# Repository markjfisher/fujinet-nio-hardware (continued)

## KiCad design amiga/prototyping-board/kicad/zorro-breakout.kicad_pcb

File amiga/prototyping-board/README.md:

# Passive Amiga Zorro-II breakout — revision A

Open [kicad/zorro-breakout.kicad_pro](kicad/zorro-breakout.kicad_pro) in KiCad 10.
The schematic and PCB use project-local symbol and footprint libraries; no
downloaded library is required. All 100 physical edge contacts are exposed.
There are **no active components, buffers, level shifters, termination,
regulators, memory or AutoConfig logic**, and no development-module footprint.

**FABRICATION-READY for a prototype spin, not hardware-tested or production-qualified.**
Read [reference-review.md](docs/reference-review.md) for the pin-map corrections
and mechanical findings, and [fabrication notes](fabrication/README.md) before
using the fabrication outputs. Nothing has been ordered or manufactured.

The [two-layer conversion review](docs/two-layer-review.md) records the
before/after measurements, return-path trade-offs and cost limitations.

The follow-up [mechanical cross-check](docs/mechanical-cross-check.md) measures
VA2000, RIPPLE-IDE, AmigaSID and the EATX socket against this board and
Commodore drawings. A-5 controls the released geometry; PCBWay is the target
fabricator and WingTAT ED100BGFBK the mating socket. Actual seating/wipe and
host operation remain prototype validation items.

## Files

* `kicad/`: editable schematic, two-layer PCB, project and local libraries.
* `data/pin-map.csv`: independently transcribed/reviewed Appendix K pin map.
* `data/verification.csv`: each physical contact → net → footprint pad →
  every matching header/test-point pad, including shared grounds and +5V.
* `data/bom.csv`: passive assembly parts. Headers may be omitted for direct
  probe access or replaced with compatible 2.54 mm sockets.
* `review/`: schematic PDF, PCB views, ERC/DRC reports and consistency result.
* `fabrication/`: copper, mask, silk and outline Gerbers; Excellon drill file,
  drill map and fabrication instructions.
* `scripts/`: reproducible generation, routing import, verification and export.
* `routing/`: Specctra input/session retained to reproduce routed copper.

## Finding signals

View the **component side**, insertion edge down: pin 100 is at the left end,
pin 2 at the right. **Pin 1 is on the reverse, directly opposite pin 2.**
The board does not have a key that prevents reversed insertion. Verify your
A500-to-Zorro-II adapter's orientation before insertion. An A500's native
86-pin expansion connector is not this 100-pin connector.

| Header | Group | Rows, top to bottom |
|---|---|---|
| J2 | ADDRESS | A1–A23, GND |
| J3 | DATA | D0–D15, GND |
| J4 | BUS CONTROL | /AS, /UDS, /LDS, READ, /DTACK, /OVR, XRDY, /RESET, /HLT, /BERR, FC0, FC1, FC2, DOE, /BUSRST, GND |
| J5 | AUTOCONFIG / SLOT CONTROL | /SLAVE, /CFGIN, /CFGOUT, GND |
| J6 | INTERRUPTS | /INT2, /INT6, GND |
| J7 | DMA / ARBITRATION | /OWN, /BR, /BGACK, /BG, /GBG, GND |
| J8 | CLOCKS | /C3, CDAC, /C1, E, 7M, GND |
| J9 | POWER | +5V, +5V, GND, GND, GND, GND |
| J10 | RESERVED / LEGACY | Reserved 40, 42, 44, 96; legacy /VPA 48, /VMA 51; NC 97, 98; SenseZ3 91; GND |
| TP1 / TP2 / TP3 | Auxiliary POWER | -5V / +12V / -12V, respectively |

**On two-column headers, both pins in each horizontal pair carry the SAME
signal. They are not signal-and-ground pairs.** J4/J5/J6/J8 provide duplicate
access for a development connection and a logic analyser. The rectangular
pad is header pin 1; pairs are numbered 1/2, 3/4, etc. The numbers next to
signal names on the board are **Zorro contact numbers**, not header indices.
J9 similarly provides four +5V pins and eight ground pins.

Important corrections to the starting map: **28=A7, 29=A1**; 96 is Reserved
with a legacy /EINT1 alias. Pin 91 is **not** connected to the PCB ground
plane: only a Zorro-II backplane grounds it. See the reference review for all
aliases and the reason to distinguish physical names from Zorro-II names.

## Connecting and probing

**DO NOT CONNECT DIRECTLY TO 3.3V LOGIC WITHOUT CHECKING ELECTRICAL
COMPATIBILITY.** This applies to the Core2350B/RP2350B board, an ESP32-S3 and
the logic analyser itself. This breakout makes no electrical conversion or
protection. Provide the required external interface before attaching logic.

Power the Amiga off before inserting/removing the card or moving jumpers.
Check board orientation, shorts between supply rails and ground, and
continuity through the adapter before powering up. Do not feed a USB module's
5V supply back into the Amiga's +5V rail. The auxiliary rails are test-only;
their presence and current budget depend on the host/adapter.

Keep probe and jumper leads short and use a nearby labelled GND. Prefer
high-impedance, low-capacitance inputs; each attached probe/board adds bus
loading. Top/bottom GND pours help return paths but are interrupted by signal routing.
They do not provide the old uninterrupted inner plane or certify bus
timing or signal integrity. The routed stubs and external wiring must be
evaluated on the intended machine. This is not a ribbon-cable extension bus.
No rail output current rating has been established by a thermal test.

The card does not respond to AutoConfig, drive /SLAVE, request DMA, assert
an interrupt, or drive any clock/control signal by itself. **/CFGIN and
/CFGOUT are separate nets.** Inserting this passive board can interrupt
configuration of cards farther down the chain. For passive-only use with
downstream cards, an external jumper from J5.3 (/CFGIN) to J5.5 (/CFGOUT)
passes the chain through. Fit it only with power off and no external circuit
driving either line; remove it before testing external AutoConfig logic.
No jumper is fitted or implied by the design.

Reserved and NC contacts are brought out for completeness, not permission to
drive them. NC 97/98 can carry signals in Zorro-III operation. /VPA and /VMA
are legacy functions unavailable in A3000 Zorro-II cycles. SenseZ3 may float
on a Zorro-III backplane; this board deliberately adds no pull-up.

The board is 180 mm wide, 100 mm above the connector shoulder, with a
129.26 ±0.1 mm tongue projecting 7.62 mm, R1.5 roots and 1.5 ×45° planar
corner chamfers. Fingers are 1.6 ×5 mm with a 1 mm tip setback. Machine
0.5 ×45° per face; 0.6 mm centre land is a derived nominal reference only.
Continuous mask windows and selective hard gold are specified in the fabrication notes.
It omits an enclosure bracket and
full-length card guide tabs; support the board and attached leads during
bench use. Case/adapter fit and physical insertion have not been tested.

## Reproducing checks

From this directory in the workspace:

```sh
source ../../../../scripts/env.sh   # finds the workspace from its own location
python scripts/check.py
```

The check exports fresh schematic connectivity, runs the independent mapping
and geometry assertions (including five negative cases), then KiCad ERC and
DRC with schematic parity. It does not regenerate or reroute the board.
Reports include warnings and fail on any unresolved violation; no DRC/ERC
exclusions are added by this project. J1 alone allows intentional mask
bridges for the continuous gold-finger window.

To reproduce the CAD **overwriting generated design files**, run
`python scripts/generate.py`, followed by `python scripts/import-routing.py`
and the check above. Reuse the stored routing session only while connector
placement, nets and mechanics are unchanged. `generate.py` explicitly resets
the PCB to its placement/fan-out state; it must not be used to update text on
a manually edited board without preserving those edits first.

For a mechanical-only reapplication, `python scripts/mechanics.py` preserves
pad positions, nets and tracks/vias; it updates the outline, finger widths,
mask openings and local connector library without regenerating the schematic.
The generator also uses this mechanical definition. The stored routing session and hash-bound completion paths reproduce the
current two-layer board; see `routing/README.md`.

Routing uses local Freerouting 2.4.1 via DSN/SES. It is not needed for opening,
checking or exporting the finished project. See `routing/README.md` for the
exact command. `python scripts/export.py` rebuilds review/fabrication outputs
after the checks pass. No export script contacts a board manufacturer.

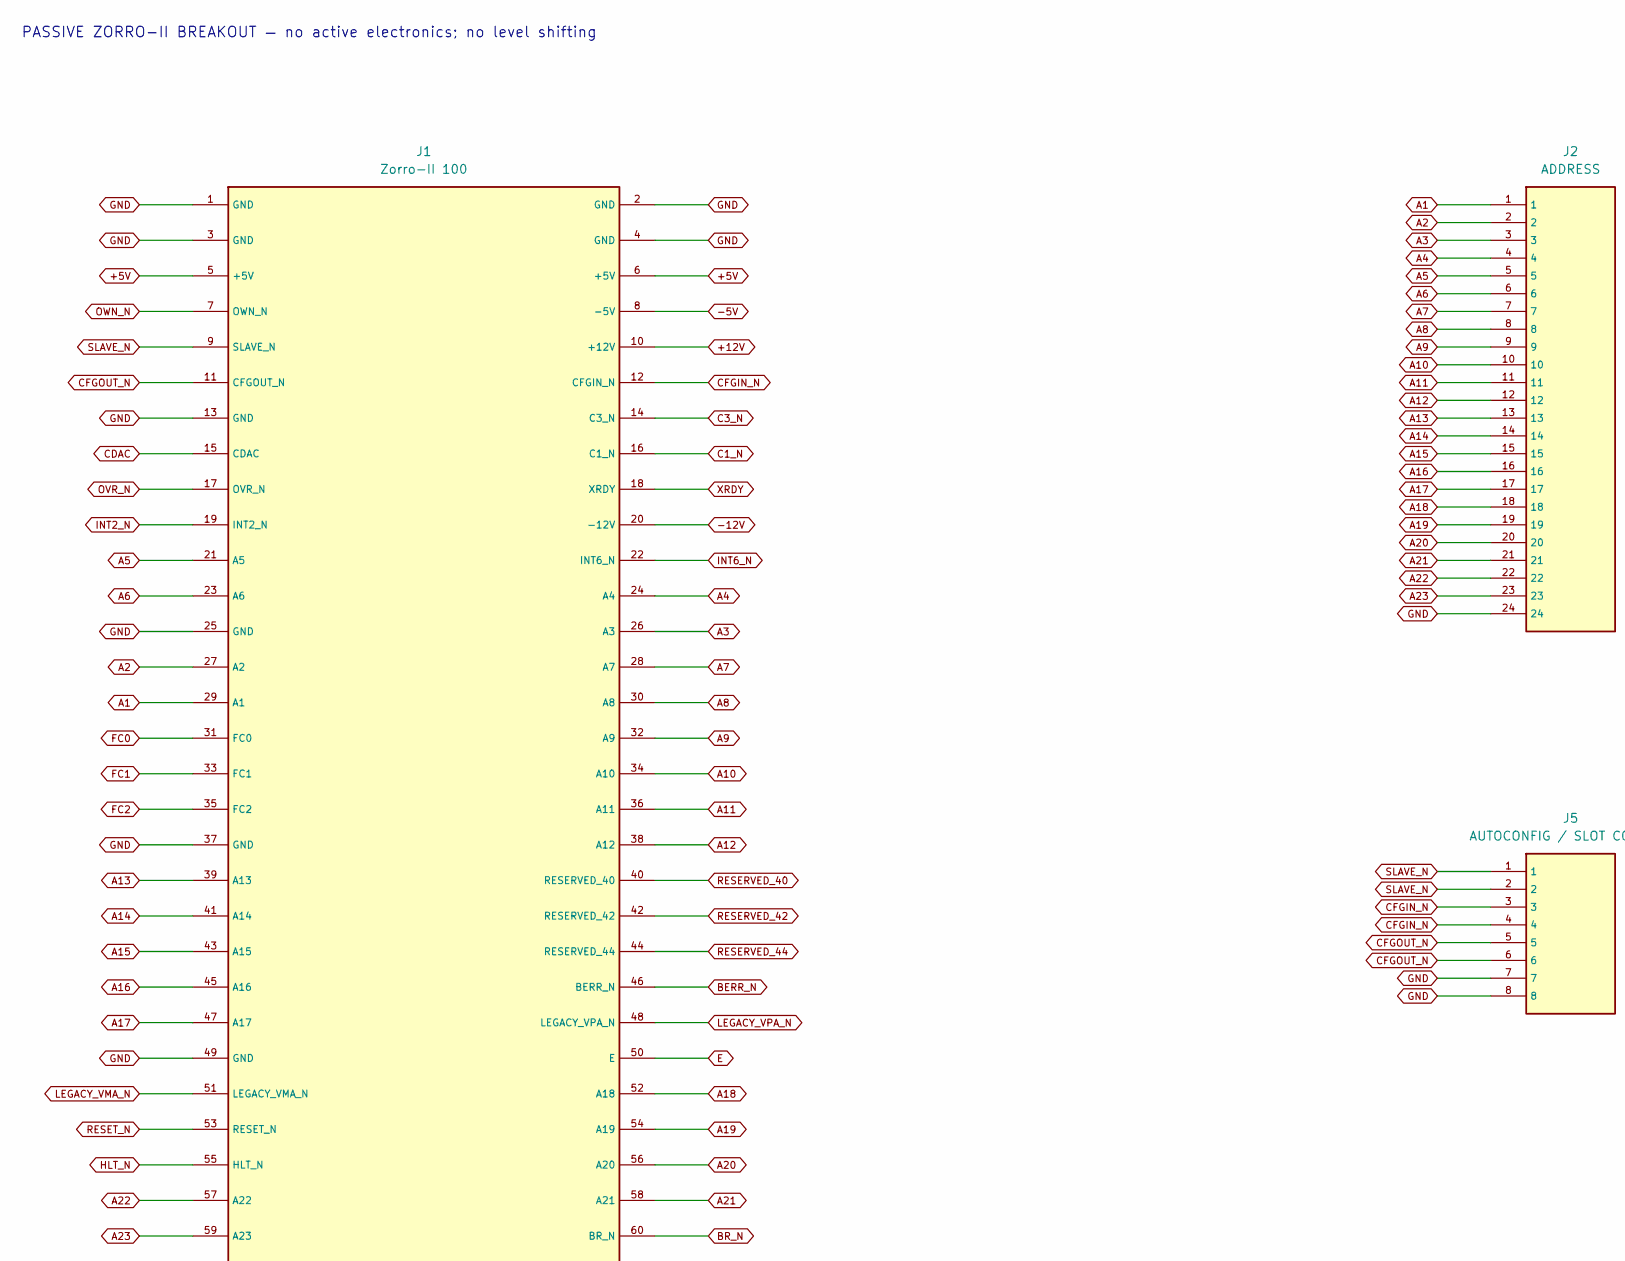
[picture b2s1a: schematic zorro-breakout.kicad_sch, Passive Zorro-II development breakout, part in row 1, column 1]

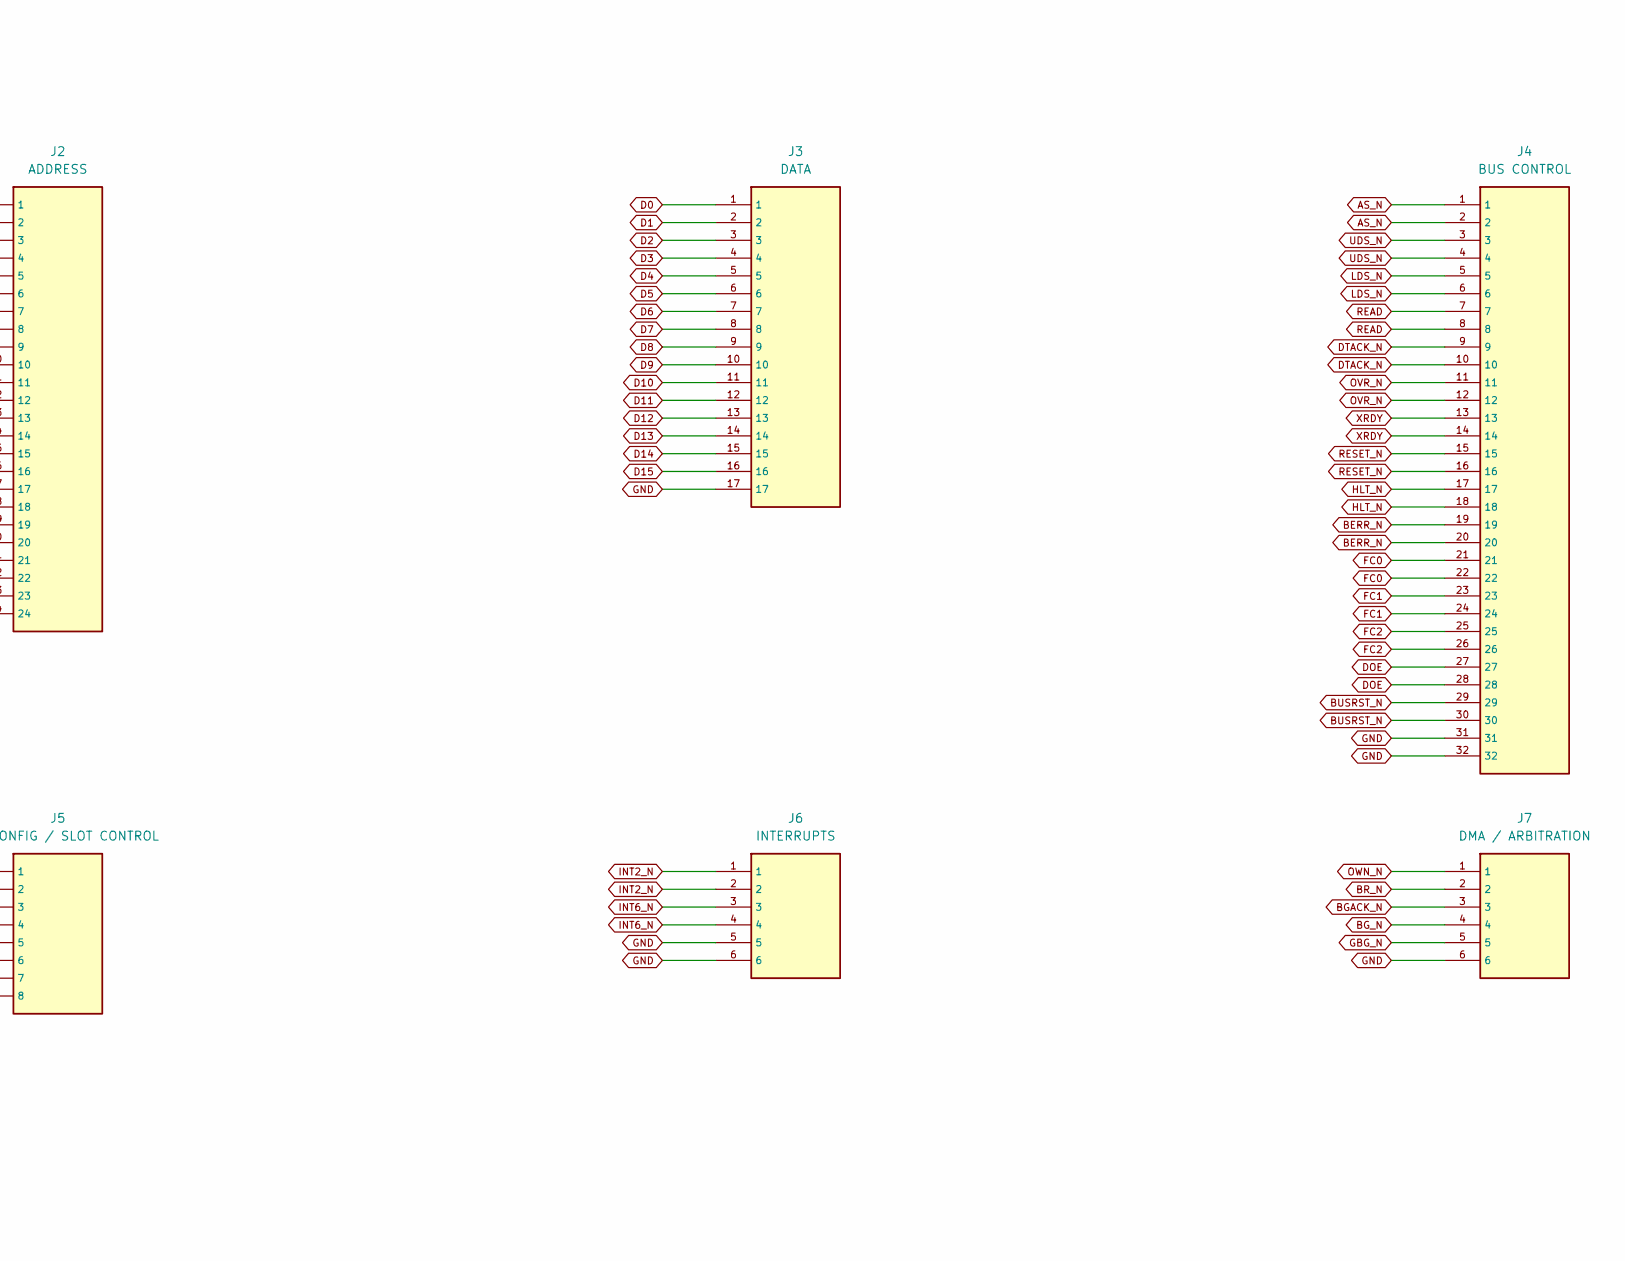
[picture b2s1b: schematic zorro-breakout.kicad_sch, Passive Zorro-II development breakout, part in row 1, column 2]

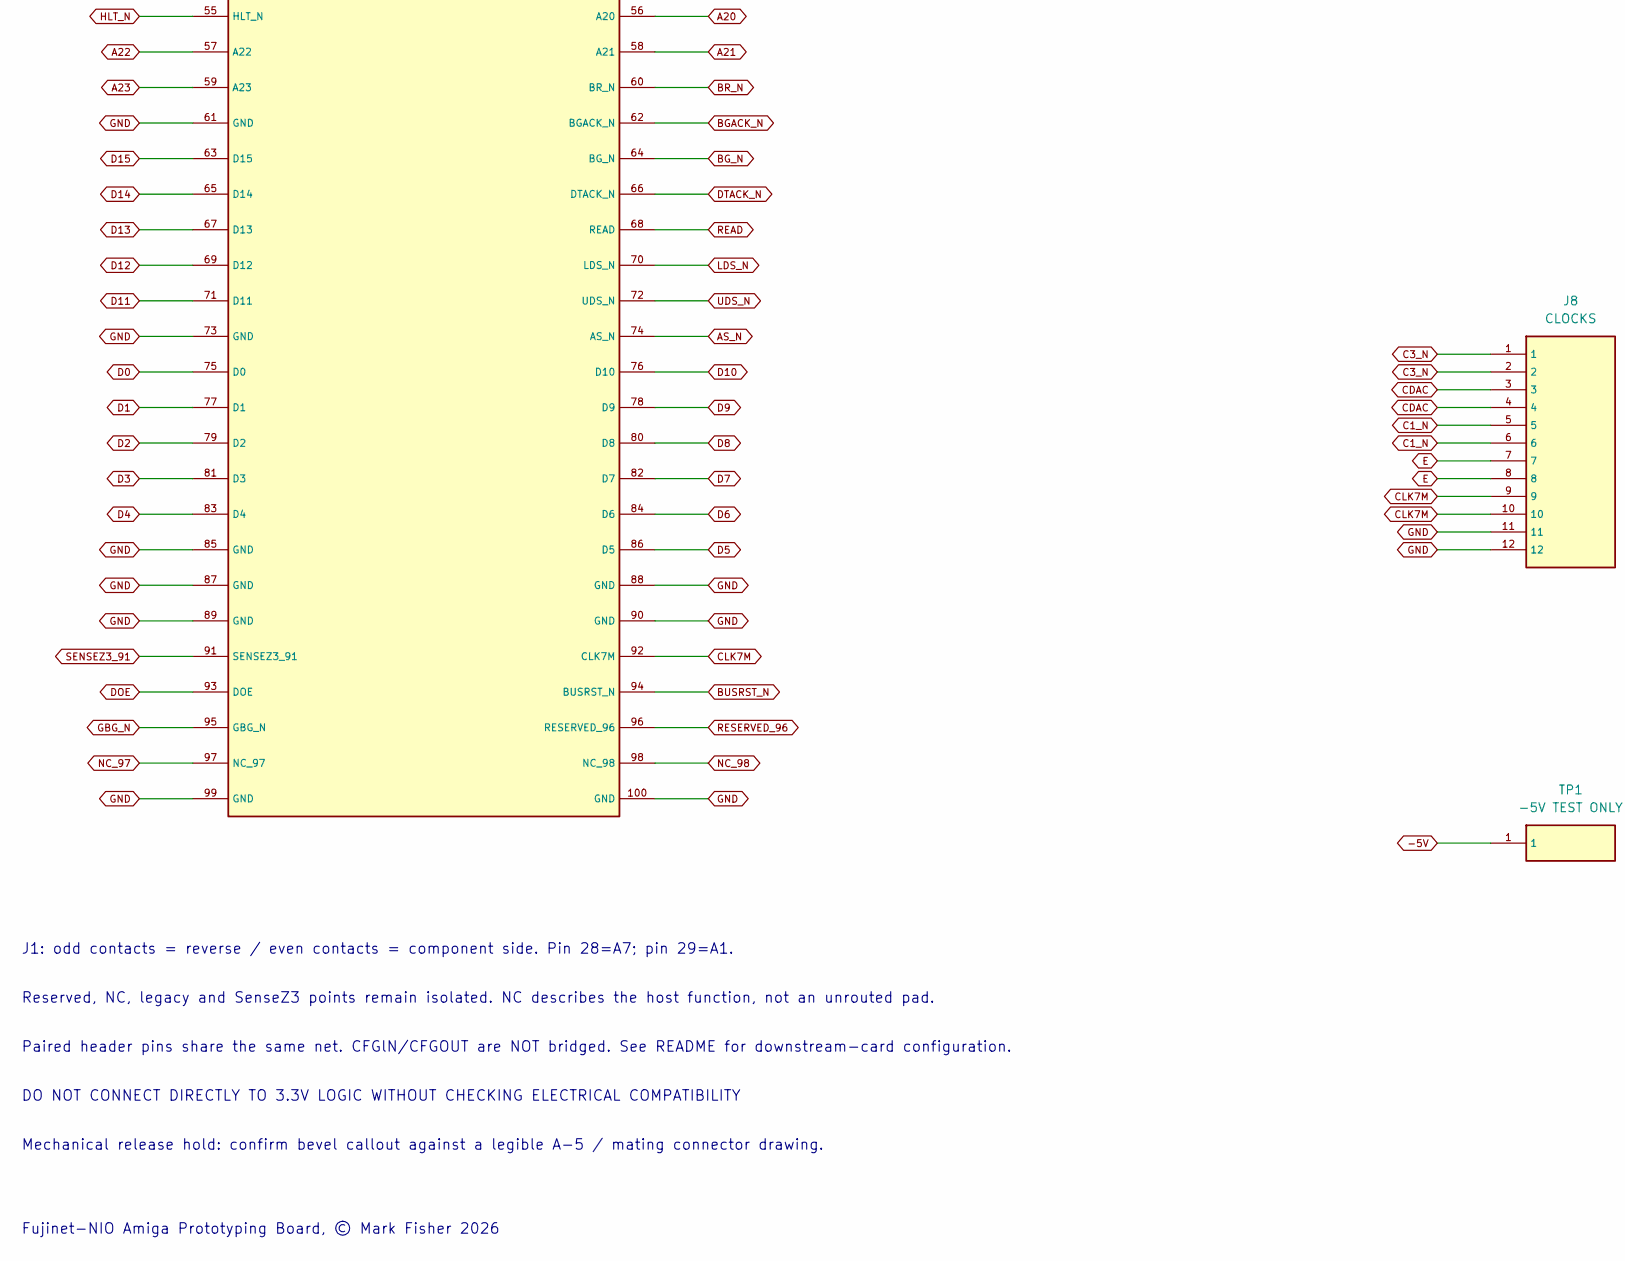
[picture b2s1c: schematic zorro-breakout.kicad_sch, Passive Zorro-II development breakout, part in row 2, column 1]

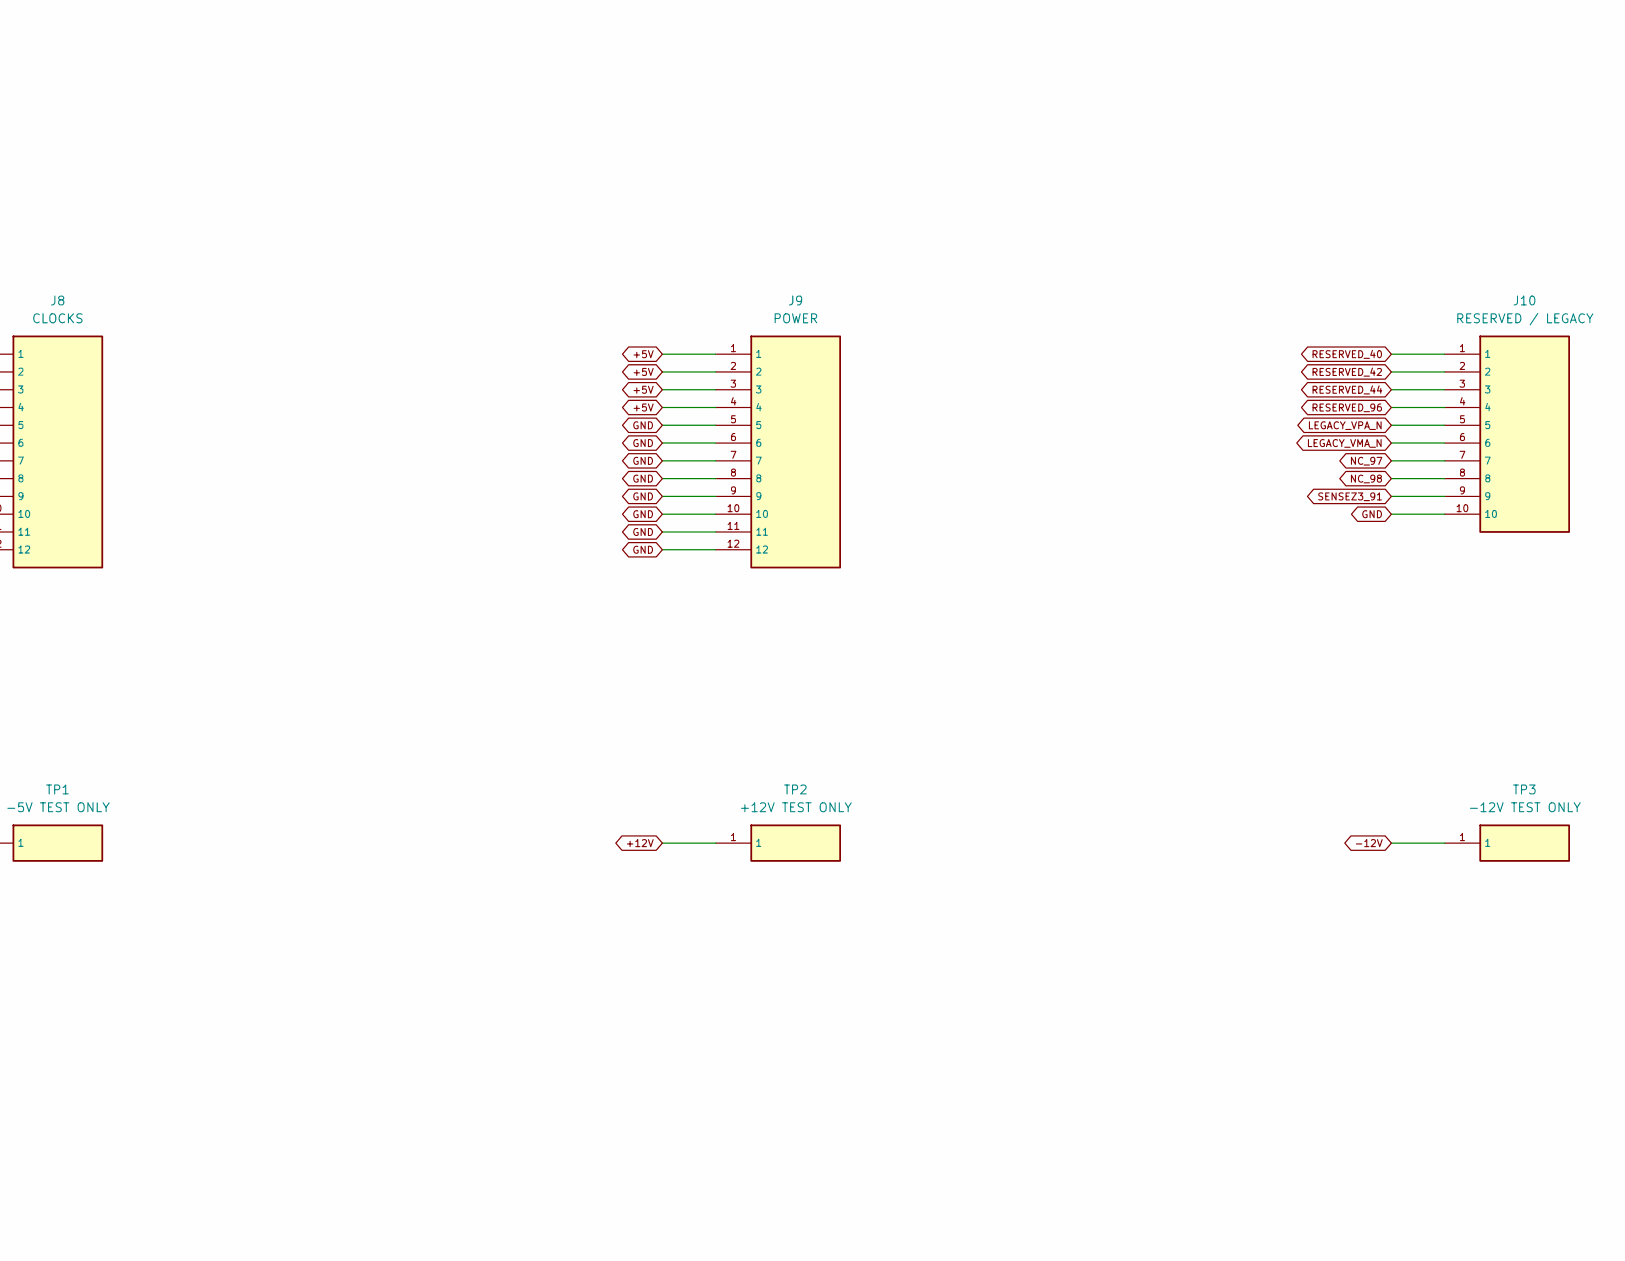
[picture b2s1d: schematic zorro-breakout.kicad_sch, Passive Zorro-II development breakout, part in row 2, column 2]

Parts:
J1: Zorro-II 100; Zorro_II_100
J2: ADDRESS; Header_1x24
J3: DATA; Header_1x17
J4: BUS CONTROL; Header_2x16
J5: AUTOCONFIG / SLOT CONTROL; Header_2x04
J6: INTERRUPTS; Header_2x03
J7: DMA / ARBITRATION; Header_1x06
J8: CLOCKS; Header_2x06
J9: POWER; Header_2x06
J10: RESERVED / LEGACY; Header_1x10
TP1: -5V TEST ONLY; Header_1x01
TP2: +12V TEST ONLY; Header_1x01
TP3: -12V TEST ONLY; Header_1x01

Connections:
+5V: J1.5 (+5V), J1.6 (+5V), J9.1, J9.2, J9.3, J9.4
+12V: J1.10 (+12V), TP2.1
-5V: J1.8 (-5V), TP1.1
-12V: J1.20 (-12V), TP3.1
A1: J1.29 (A1), J2.1
A2: J1.27 (A2), J2.2
A3: J1.26 (A3), J2.3
A4: J1.24 (A4), J2.4
A5: J1.21 (A5), J2.5
A6: J1.23 (A6), J2.6
A7: J1.28 (A7), J2.7
A8: J1.30 (A8), J2.8
A9: J1.32 (A9), J2.9
A10: J1.34 (A10), J2.10
A11: J1.36 (A11), J2.11
A12: J1.38 (A12), J2.12
A13: J1.39 (A13), J2.13
A14: J1.41 (A14), J2.14
A15: J1.43 (A15), J2.15
A16: J1.45 (A16), J2.16
A17: J1.47 (A17), J2.17
A18: J1.52 (A18), J2.18
A19: J1.54 (A19), J2.19
A20: J1.56 (A20), J2.20
A21: J1.58 (A21), J2.21
A22: J1.57 (A22), J2.22
A23: J1.59 (A23), J2.23
AS_N: J1.74 (AS_N), J4.1, J4.2
BERR_N: J1.46 (BERR_N), J4.19, J4.20
BGACK_N: J1.62 (BGACK_N), J7.3
BG_N: J1.64 (BG_N), J7.4
BR_N: J1.60 (BR_N), J7.2
BUSRST_N: J1.94 (BUSRST_N), J4.29, J4.30
C1_N: J1.16 (C1_N), J8.5, J8.6
C3_N: J1.14 (C3_N), J8.1, J8.2
CDAC: J1.15 (CDAC), J8.3, J8.4
CFGIN_N: J1.12 (CFGIN_N), J5.3, J5.4
CFGOUT_N: J1.11 (CFGOUT_N), J5.5, J5.6
CLK7M: J1.92 (CLK7M), J8.9, J8.10
D0: J1.75 (D0), J3.1
D1: J1.77 (D1), J3.2
D2: J1.79 (D2), J3.3
D3: J1.81 (D3), J3.4
D4: J1.83 (D4), J3.5
D5: J1.86 (D5), J3.6
D6: J1.84 (D6), J3.7
D7: J1.82 (D7), J3.8
D8: J1.80 (D8), J3.9
D9: J1.78 (D9), J3.10
D10: J1.76 (D10), J3.11
D11: J1.71 (D11), J3.12
D12: J1.69 (D12), J3.13
D13: J1.67 (D13), J3.14
D14: J1.65 (D14), J3.15
D15: J1.63 (D15), J3.16
DOE: J1.93 (DOE), J4.27, J4.28
DTACK_N: J1.66 (DTACK_N), J4.9, J4.10
E: J1.50 (E), J8.7, J8.8
FC0: J1.31 (FC0), J4.21, J4.22
FC1: J1.33 (FC1), J4.23, J4.24
FC2: J1.35 (FC2), J4.25, J4.26
GBG_N: J1.95 (GBG_N), J7.5
GND: J1.1 (GND), J1.2 (GND), J1.3 (GND), J1.4 (GND), J1.13 (GND), J1.25 (GND), J1.37 (GND), J1.49 (GND), J1.61 (GND), J1.73 (GND), J1.85 (GND), J1.87 (GND), J1.88 (GND), J1.89 (GND), J1.90 (GND), J1.99 (GND), J1.100 (GND), J2.24, J3.17, J4.31, J4.32, J5.7, J5.8, J6.5, J6.6, J7.6, J8.11, J8.12, J9.5, J9.6, J9.7, J9.8, J9.9, J9.10, J9.11, J9.12, J10.10
HLT_N: J1.55 (HLT_N), J4.17, J4.18
INT2_N: J1.19 (INT2_N), J6.1, J6.2
INT6_N: J1.22 (INT6_N), J6.3, J6.4
LDS_N: J1.70 (LDS_N), J4.5, J4.6
LEGACY_VMA_N: J1.51 (LEGACY_VMA_N), J10.6
LEGACY_VPA_N: J1.48 (LEGACY_VPA_N), J10.5
NC_97: J1.97 (NC_97), J10.7
NC_98: J1.98 (NC_98), J10.8
OVR_N: J1.17 (OVR_N), J4.11, J4.12
OWN_N: J1.7 (OWN_N), J7.1
READ: J1.68 (READ), J4.7, J4.8
RESERVED_40: J1.40 (RESERVED_40), J10.1
RESERVED_42: J1.42 (RESERVED_42), J10.2
RESERVED_44: J1.44 (RESERVED_44), J10.3
RESERVED_96: J1.96 (RESERVED_96), J10.4
RESET_N: J1.53 (RESET_N), J4.15, J4.16
SENSEZ3_91: J1.91 (SENSEZ3_91), J10.9
SLAVE_N: J1.9 (SLAVE_N), J5.1, J5.2
UDS_N: J1.72 (UDS_N), J4.3, J4.4
XRDY: J1.18 (XRDY), J4.13, J4.14

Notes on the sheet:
PASSIVE ZORRO-II BREAKOUT — no active electronics; no level shifting
J1: odd contacts = reverse / even contacts = component side. Pin 28=A7; pin 29=A1.
Reserved, NC, legacy and SenseZ3 points remain isolated. NC describes the host function, not an unrouted pad.
Paired header pins share the same net. CFGlN/CFGOUT are NOT bridged. See README for downstream-card configuration.
DO NOT CONNECT DIRECTLY TO 3.3V LOGIC WITHOUT CHECKING ELECTRICAL COMPATIBILITY
Mechanical release hold: confirm bevel callout against a legible A-5 / mating connector drawing.
Fujinet-NIO Amiga Prototyping Board, © Mark Fisher 2026

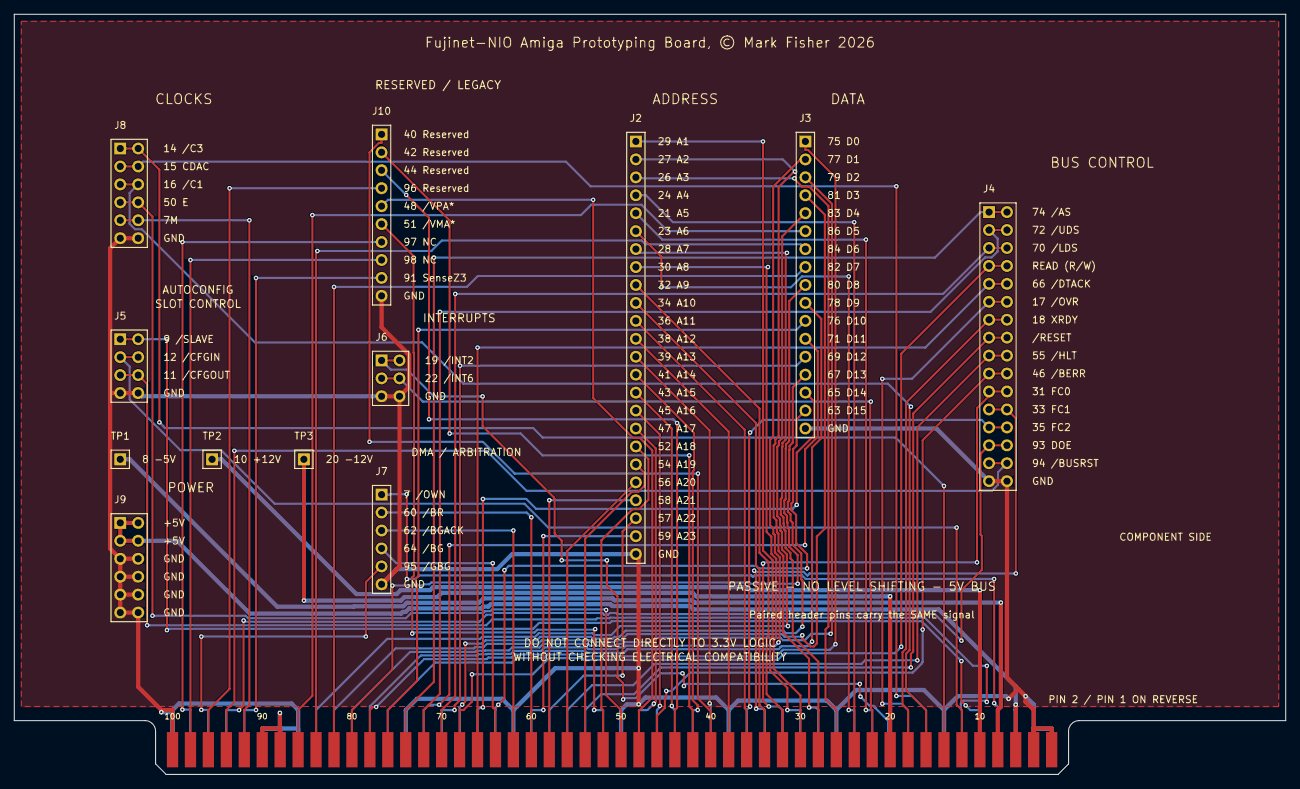
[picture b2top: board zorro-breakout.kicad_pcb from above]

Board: 2 copper layers, 180.0 x 107.6 mm, 13 parts (0 on the bottom side), 83 nets.

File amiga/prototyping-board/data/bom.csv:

reference,quantity,description,footprint,notes
PCB,1,Passive Zorro-II breakout revision A,180 x 107.62 mm overall,4 layers; 1.6 mm; see fabrication notes
J1,1,Integral 100-contact Zorro card edge,Zorro_II_100,Part of PCB; not a purchased connector
J2,1,2.54 mm vertical pin header 1x24,Header_1x24,Cut-to-length strip
J3,1,2.54 mm vertical pin header 1x17,Header_1x17,Cut-to-length strip
J4,1,2.54 mm vertical pin header 2x16,Header_2x16,Horizontal pairs carry identical signals
J5,1,2.54 mm vertical pin header 2x04,Header_2x04,Horizontal pairs carry identical signals
J6,1,2.54 mm vertical pin header 2x03,Header_2x03,Horizontal pairs carry identical signals
J7,1,2.54 mm vertical pin header 1x06,Header_1x06,Cut-to-length strip
J8 J9,2,2.54 mm vertical pin header 2x06,Header_2x06,Horizontal pairs carry identical signals
J10,1,2.54 mm vertical pin header 1x10,Header_1x10,Reserved and legacy contacts
TP1 TP2 TP3,3,Single test pin or 2.54 mm header post,Header_1x01,1 mm finished hole; auxiliary supply rails only

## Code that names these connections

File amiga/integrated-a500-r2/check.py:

"""Independent native KiCad connectivity, ERC and hardware-logic checks. No CAD edits."""
import csv
import itertools
import json
from pathlib import Path
import subprocess
import xml.etree.ElementTree as ET
from collections import defaultdict
ROOT=Path(__file__).resolve().parent
REVIEW=ROOT/'review'
SCH=ROOT/'integrated-a500-r2.kicad_sch'
def run(*args):subprocess.run(args,check=True,cwd=ROOT,capture_output=True,text=True)
def main():
 plan=json.loads((ROOT/'circuit.json').read_text())
 run('kicad-cli','sch','export','netlist','--format','kicadxml','-o',str(REVIEW/'netlist.xml'),str(SCH))
 run('kicad-cli','sch','erc','--format','json','-o',str(REVIEW/'erc.json'),str(SCH))
 tree=ET.parse(REVIEW/'netlist.xml');actual={};nets={}
 for n in tree.findall('./nets/net'):
  nets[n.get('name')]={(p.get('ref'),p.get('pin')) for p in n.findall('node')}
  for key in nets[n.get('name')]:
   assert key not in actual,key
   actual[key]=n.get('name')
 expected=defaultdict(set)
 for c in plan['components']:
  if c['reference'].startswith('#'):continue
  for pin,n in c['pins'].items():expected[n].add((c['reference'],pin))
 # Whole-net membership, not merely labels or a count of parts. This catches
 # accidental shorts, disconnected hierarchy and duplicated local net names.
 for name,pins in expected.items():
  connected={actual.get(k) for k in pins}
  assert len(connected)==1 and None not in connected,(name,connected,pins)
  net=connected.pop()
  assert net.rsplit('/',1)[-1]==name,(name,net)
  assert nets[net]==pins,(name,'unexpected/missing members',nets[net]^pins)
 a={key:net.rsplit('/',1)[-1] for key,net in actual.items()}
 assert {p for r,p in actual if r=='U20'}=={str(i) for i in range(1,82)}
 assert len({a['U20',str(i)] for i in range(1,82)})==len(set(next(c for c in plan['components'] if c['reference']=='U20')['pins'].values()))
 assert [a['U20',str(i)] for i in [79,80,1,2,3,4]]==[f'Z_A{i}' for i in range(2,8)]
 assert a['U20','56']=='IRQ_REQ' and a['U20','57']=='BUS_READY'
 assert a['U20','66']=='RP_USB_DM' and a['U20','67']=='RP_USB_DP'
 # Logic evaluation uses IC pin membership exported by KiCad and the
 # manufacturer's pin functions. It does not use the proposed gate-net list.
 order=[f'U{i}' for i in range(61,64)]+['U85']+[f'U{i}' for i in range(64,84)]
 kinds={c['reference']:c['lib_id'].split('74LVC1G')[-1] for c in plan['components'] if c['reference'] in order}
 def evaluate(inputs):
  v=dict(inputs,**{'3V3':1,'GND':0})
  for r in order:
   k=kinds[r];ps=['1','3','6'] if k in ('10','11') else (['1','2'] if k in ('08','32') else ['2'])
   b=[v[a[r,p]] for p in ps]
   out=(not b[0]) if k in ('04','06') else ((not all(b)) if k=='10' else (any(b) if k=='32' else all(b)))
   v[a[r,'4']]=int(out)
  return v
 safe_inputs=['HOST_PG','3V3_PG','HOST_RESET_N','RP_RUN','RUN_MODE','BUS_ARM','BUS_READY','HOST_BERR_N']
 cases=0
 for safe_bits in itertools.product([0,1],repeat=8):
  for as_n,rd,drive,lds,uds,ack,irq,window in itertools.product([0,1],repeat=8):
   x=dict(zip(safe_inputs,safe_bits))
   x.update(Z_AS_N=as_n,Z_READ=rd,DATA_VALID=drive,Z_LDS_N=lds,Z_UDS_N=uds,WAIT_PENDING=not ack,IRQ_REQ=irq,
            Z_A23=window,Z_A22=1,Z_A21=1,Z_A20=0,Z_A19=1)
   v=evaluate(x);safe=all(safe_bits);cycle=safe and not as_n and window
   assert v['TX_LO_N']==int(not(cycle and rd and drive and not lds))
   assert v['TX_HI_N']==int(not(cycle and rd and drive and not uds))
   assert v['RX_LO_N']==int(not(cycle and not rd and not drive and not lds))
   assert v['RX_HI_N']==int(not(cycle and not rd and not drive and not uds))
   assert v['AMIGA_XRDY']==int(not(cycle and not ack))
   assert v['AMIGA_INT2_N']==int(not(safe and irq))
   assert not(v['TX_LO_N']==0 and v['RX_LO_N']==0)
   assert not(v['TX_HI_N']==0 and v['RX_HI_N']==0)
   cases+=1
 # No board output may drive DTACK. The existing receive buffer is observation only.
 assert expected['AMIGA_DTACK_N']=={('J40','66'),('U43','7')}
 # Manufacturer pin functions: CLK1 D2 /Q3 GND4 Q5 /CLR6 /PRE7 VCC8.
 # Evaluate asynchronous clear and positive edges from saved net membership.
 def latch_step(ref, values, q, previous_clock):
  assert a[ref,'7']=='3V3' and a[ref,'8']=='3V3' and a[ref,'4']=='GND'
  clk=values[a[ref,'1']]
  if not values[a[ref,'6']]:q=0
  elif clk and not previous_clock:q=values[a[ref,'2']]
  return q,clk
 sequential_cases=0
 for ref,clock,pin in [('U84','ACK_REQ','3'),('U86','DATA_DRIVE','5')]:
  assert a[ref,'6']=='CYCLE_OK'
  assert a[ref,pin]==('WAIT_PENDING' if ref=='U84' else 'DATA_VALID')
  # Exhaust five-step sequences of cycle qualification, request and lane state.
  # Includes requests stuck high over back-to-back cycles and asynchronous aborts.
  for events in itertools.product(range(8),repeat=5):
   q=previous=0;reference_q=0;last_request=0
   for e in events:
    cycle,request,lane=(e>>2)&1,(e>>1)&1,e&1
    v={'3V3':1,'CYCLE_OK':cycle,'ANY_LANE':lane,clock:request}
    q,previous=latch_step(ref,v,q,previous)
    if not cycle:reference_q=0
    elif request and not last_request:reference_q=lane if ref=='U84' else 1
    assert q==reference_q
    last_request=request
   sequential_cases+=1
 # Exhaust the five high address bits independently of the safety-state loop.
 for bits in itertools.product([0,1],repeat=5):
  x.update(dict(zip(['Z_A23','Z_A22','Z_A21','Z_A20','Z_A19'],bits)))
  assert evaluate(x)['IO_WINDOW']==int(bits==(1,1,1,0,1))
 # USB paths, both polarities, all physical flash selections.
 for rp,esp,wanted in [(0,0,{('ESP','RP')}),(1,0,{('PC','RP')}),(0,1,{('ESP','PC')}),(1,1,set())]:
  for polarity,common,p1,p2 in [('DP','4','2','3'),('DM','6','8','7')]:
   graph=defaultdict(set)
   for r,sel,oe in [('U1',rp,esp),('U2',esp,rp)]:
    if oe:continue
    u,w=a[r,common],a[r,p2 if sel else p1];graph[u].add(w);graph[w].add(u)
   pairs=set()
   for src in ['PC','RP','ESP']:
    seen=set();todo=[src+'_'+polarity]
    while todo:
     node=todo.pop()
     if node not in seen:seen.add(node);todo.extend(graph[node]-seen)
    for dst in ['PC','RP','ESP']:
     if dst!=src and dst+'_'+polarity in seen:pairs.add(tuple(sorted((src,dst))))
   assert pairs==wanted,(rp,esp,polarity,pairs)
 # ERC findings are retained, not excluded or called a clean pass. Restrict the
 # known model limitation to external A500 inputs and off-sheet pull-ups.
 erc=json.loads((REVIEW/'erc.json').read_text())
 violations=[v for s in erc['sheets'] for v in s['violations']]
 allowed={18,19,46,53,66,68,70,72,74,29,27,26,24,21,23,28,30,32,34,36,38,39,41,43,45,47,52,54,56,58,57,59}
 import re
 found=set()
 for v in violations:
  assert v['type']=='pin_not_driven',v
  assert len(v['items'])==1,v
  m=re.match(r'Symbol J40 Pin (\d+) ',v['items'][0]['description']);assert m,v
  found.add(int(m[1]))
 assert found==allowed,(found,allowed)
 run('kicad-cli','sch','export','pdf','-o',str(REVIEW/'schematic.pdf'),str(SCH))
 rows=list(csv.DictReader((ROOT.parent/'integrated-r0/rp2350-pin-allocation.csv').open()))
 for r in rows:
  r['candidate_net']=a['U20',r['package_pad']]
  if r['package_pad']=='55':r['function']='completion pulse; rising edge releases XRDY for this cycle; external pulldown'
  if r['package_pad']=='58':r['function']='read-claim pulse; per-cycle latch; external pulldown'
  if r['package_pad']=='59':r['function']='analog supply; local decoupling'
  if r['package_pad']=='61':r['function']='regulator analog supply; 33-ohm/4.7uF filter'
 with (ROOT/'rp2350-pin-allocation.csv').open('w') as f:
  w=csv.DictWriter(f,fieldnames=rows[0].keys(),lineterminator="\n");w.writeheader();w.writerows(rows)
 result=dict(scope='A500 R2 circuit candidate; NOT electrical/layout release',components=len(tree.findall('./components/comp')),
  checked_physical_pin_assignments=sum(map(len,expected.values())),exact_nets=len(expected),rp_package_pads=81,
  bus_logic_cases=cases,sequential_cases=sequential_cases,address_decode_cases=32,usb_cases=8,erc_findings_retained=len(violations),
  erc_status=f'{len(violations)} external A500 driver/pull-up model findings; no exclusions; not zero ERC',
  pcb='not implemented; DRC and parity not applicable')
 (REVIEW/'checks.json').write_text(json.dumps(result,indent=2)+'\n');print(json.dumps(result,indent=2))
if __name__=='__main__':main()

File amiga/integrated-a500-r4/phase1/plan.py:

"""Incremental electrical edits, not a placement/board generator."""
import json,copy
from pathlib import Path
P=Path(__file__).resolve().parent.parent
base=json.loads((P/'phase1/baseline-plan.json').read_text())
C={c['reference']:c for c in base['components']}
stages=[]
def stage(name):
 s={'name':name,'remove':[],'add':[],'rewire':[],'update':[]};stages.append(s);return s
def rm(s,*refs):
 for r in refs:s['remove'].append(copy.deepcopy(C.pop(r)))
def add(s,r,lib,val,pins,fp,page='guard',position=None):
 c=dict(reference=r,lib_id=lib,value=val,pins={str(k):v for k,v in pins.items()},footprint=fp,page=page,position=position or [50+len(s['add'])%7*100,60+len(s['add'])//7*60],rotation=0)
 assert r not in C,r
 C[r]=c;s['add'].append(copy.deepcopy(c))
def rw(s,r,p,n):
 c=C[r];old=c['pins'].get(str(p));s['rewire'].append(dict(reference=r,page=c['page'],pin=str(p),old=old,new=n));c['pins'].pop(str(p),None) if n is None else c['pins'].__setitem__(str(p),n)

def upd(s,r,**kw):
 s['update'].append(dict(reference=r,page=C[r]['page'],**kw));C[r].update(kw)
def cap(s,r,n,v='100n 10V X7R',page='guard',fp='Capacitor_SMD:C_0603_1608Metric'):add(s,r,'Device:C_Polarized' if 'polymer' in v else 'Device:C',v,{1:n,2:'GND'},fp,page)
def res(s,r,a,b,v):add(s,r,'Device:R',v,{1:a,2:b},'Resistor_SMD:R_0603_1608Metric')
def schmitt(s,r,pairs):
 pins={8:'3V3',4:'GND'}
 for (a,y),(raw,out) in zip([(1,7),(3,5),(6,2)],pairs):pins[a]=raw;pins[y]=out
 add(s,r,'Phase1:74LVC3G17','74LVC3G17DC,125',pins,'Package_SO:VSSOP-8_2.3x2mm_P0.5mm')
s=stage('protection')
rm(s,'U60','R60','R61','R62','C60','R9','U81','U83','C90','C92')
add(s,'U95','Phase1:TPS2553','TPS2553DBVR',{1:'AMIGA_5V',2:'GND',3:'AMIGA_5V',5:'HOST_ILIM',6:'HOST_5V_LIMITED'},'Package_TO_SOT_SMD:SOT-23-6')
res(s,'R110','HOST_ILIM','GND','133k 1%');cap(s,'C110','AMIGA_5V')
add(s,'D4','Device:D_Schottky','SS14-13-F',{1:'HOST_LDO_IN',2:'HOST_5V_LIMITED'},'Diode_SMD:D_SMA')
add(s,'U96','Regulator_Linear:AP2112K-3.3','AP2112K-3.3TRG1',{1:'HOST_LDO_IN',2:'GND',3:'HOST_LDO_IN',5:'3V3_BUS'},'Package_TO_SOT_SMD:SOT-23-5')
cap(s,'C111','HOST_LDO_IN','1u 10V X7R');cap(s,'C112','3V3_BUS','1u 10V X7R')
cap(s,'C113','3V3_BUS','100u 6.3V polymer 20% ESR<=50m',fp='Capacitor_SMD:CP_Elec_6.3x5.8')
res(s,'R111','3V3_BUS','GND','4.7k 1%')
for r,sense,ct,top,bot,supply,ctref,byref in [('U60','HOST_SENSE','HOST_CT','R60','R61','AMIGA_5V','C114','C60'),('U90','MAIN_SENSE','MAIN_CT','R112','R113','3V3','C115','C118'),('U91','BUS_SENSE','BUS_CT','R114','R115','3V3_BUS','C116','C119')]:
 add(s,r,'Phase1:MIC2790H','MIC2790H-04VD6-TR',{1:'GUARD_OK_RAW',2:'GND',3:'3V3_BUS',4:ct,5:sense,6:'3V3_BUS'},'Package_TO_SOT_SMD:TSOT-23-6')
 res(s,top,supply,sense,'102k 0.1%' if r=='U60' else '67.5k 0.1%');res(s,bot,sense,'GND','10k 0.1%');cap(s,ctref,ct,'100p 25V C0G 5%');cap(s,byref,'3V3_BUS','1u 10V X7R')
res(s,'R116','3V3_BUS','GUARD_OK_RAW','10k 1%')
add(s,'U92','Phase1:SN74LVC2G14','SN74LVC2G14DBVR',{1:'GUARD_OK_RAW',6:'BUS_DISABLE',3:'BUS_DISABLE',4:'BUS_PERMIT',2:'GND',5:'3V3_BUS'},'Package_TO_SOT_SMD:SOT-23-6');cap(s,'C120','3V3_BUS')
res(s,'R117','3V3_BUS','BUS_DISABLE','100k 1%');res(s,'R122','BUS_PERMIT','GND','10k 1%')
add(s,'U93','Phase1:SN74LVC2G132','SN74LVC2G132DCUR',{1:'BUS_PERMIT',2:'WAIT_SINK',7:'WAIT_OE_N',5:'BUS_PERMIT',6:'IRQ_SINK',3:'IRQ_OE_N',4:'GND',8:'3V3_BUS'},'Package_SO:VSSOP-8_2.3x2mm_P0.5mm');cap(s,'C121','3V3_BUS')
add(s,'U94','Phase1:SN74LVC2G125','SN74LVC2G125DCUR',{1:'WAIT_OE_N',2:'GND',6:'AMIGA_XRDY',7:'IRQ_OE_N',5:'GND',3:'AMIGA_INT2_N',4:'GND',8:'3V3_BUS'},'Package_SO:VSSOP-8_2.3x2mm_P0.5mm');cap(s,'C122','3V3_BUS')
res(s,'R118','3V3_BUS','WAIT_OE_N','100k 1%');res(s,'R119','3V3_BUS','IRQ_OE_N','100k 1%')
add(s,'Q5','Transistor_BJT:MMBT3904','MMBT3904-7-F',{1:'GUARD_RESET_BASE',2:'GND',3:'RP_RUN'},'Package_TO_SOT_SMD:SOT-23')
res(s,'R120','BUS_DISABLE','GUARD_RESET_BASE','22k 1%');res(s,'R121','GUARD_RESET_BASE','GND','100k 1%')
cap(s,'C117','3V3','220u 6.3V polymer 20% ESR<=50m',fp='Capacitor_SMD:CP_Elec_6.3x5.8')
for r in ['U44','U45']:rw(s,r,20,'3V3_BUS')
for r in ['C54','C55']:rw(s,r,1,'3V3_BUS')
for r in ['U44','U45','U46','U47']:rw(s,r,19,'BUS_DISABLE')
rw(s,'U5',4,None);rw(s,'U61',1,'BUS_PERMIT');rw(s,'U61',3,'BUS_PERMIT')
# Condition only released safety/mode/request inputs in this implementation.
schmitt(s,'U97',[(x,x+'_C') for x in ['RP_RUN','RUN_MODE','BUS_ARM']]);cap(s,'C125','3V3')
schmitt(s,'U98',[(x,x+'_C') for x in ['BUS_READY','DATA_DRIVE','ACK_REQ']]);cap(s,'C126','3V3')
add(s,'U99','74xGxx:74LVC1G17','SN74LVC1G17DBVR',{2:'IRQ_REQ',4:'IRQ_REQ_C',3:'GND',5:'3V3'},'Package_TO_SOT_SMD:SOT-23-5');cap(s,'C127','3V3')
for p,n in [(1,'RP_RUN_C'),(3,'RUN_MODE_C'),(6,'BUS_ARM_C')]:rw(s,'U62',p,n)
rw(s,'U63',6,'BUS_READY_C');rw(s,'U84',1,'ACK_REQ_C');rw(s,'U86',1,'DATA_DRIVE_C');rw(s,'U82',2,'IRQ_REQ_C')
# Protect slow open-collector host reset / bus-error / receive-only DTACK inputs.
schmitt(s,'U100',[(x,x+'_C') for x in ['AMIGA_RESET_N','AMIGA_BERR_N','AMIGA_DTACK_N']]);cap(s,'C128','3V3')
for pin,net in [(6,'AMIGA_RESET_N_C'),(8,'AMIGA_BERR_N_C'),(7,'AMIGA_DTACK_N_C')]:rw(s,'U43',pin,net)
# Same five-pin layout and logic polarity, real Schmitt input for CC status.
upd(s,'U7',lib_id='74xGxx:74LVC1G14',value='SN74LVC1G14DBVR')
cap(s,'C123','3V3_AON',page='power');C['C123']['position']=[350,200];s['add'][-1]['position']=[350,200]
cap(s,'C124','5V_MAIN',page='power');C['C124']['position']=[350,250];s['add'][-1]['position']=[350,250]
# Stage snapshots are pin intent, independent of native CAD export.
add(s,'#FLG10','power:PWR_FLAG','PWR_FLAG',{1:'HOST_LDO_IN'},'',position=[750,60])
s['expected']=copy.deepcopy(list(C.values()))
s=stage('I1')
for r,olds,capkeep,caps in [('U61',['U61','U62','U63'],'C70',['C71','C72']),('U66',['U66','U67','U68'],'C75',['C76','C77']),('U71',['U71','U76','U80'],'C80',['C85','C89'])]:
 pins={14:'3V3',7:'GND'};pos={'U61':[550,120],'U66':[680,120],'U71':[550,260]}[r];page=C[r]['page']
 for old,(a,b,c,y) in zip(olds,[(1,2,13,12),(3,4,5,6),(9,10,11,8)]):
  p=C[old]['pins'];pins.update({a:p['1'],b:p['3'],c:p['6'],y:p['4']})
 rm(s,*olds,*caps);add(s,r,'Phase1:SN74LVC11A','SN74LVC11APWR',pins,'Package_SO:TSSOP-14_4.4x5mm_P0.65mm',page,pos)
s['expected']=copy.deepcopy(list(C.values()))
s=stage('I2');pins={14:'3V3',7:'GND'};pos=[680,260]
for r,a,y in [('U64',1,2),('U65',3,4),('U69',5,6),('U70',9,8),('U74',11,10),('U75',13,12)]:pins[a]=C[r]['pins']['2'];pins[y]=C[r]['pins']['4']
rm(s,'U64','U65','U69','U70','U74','U75','C74','C78','C79','C83','C84');add(s,'U64','Phase1:SN74LVC04A','SN74LVC04APWR',pins,'Package_SO:TSSOP-14_4.4x5mm_P0.65mm','control',pos)
s['expected']=copy.deepcopy(list(C.values()))
for name,refs,val in [('R-A',['R37','R38','R39','R40'],'CAT16-4702F4LF'),('R-B',['R64','R65','R66','R67'],'CAT16-1002F4LF')]:
 s=stage(name);pins={};pos=[550,120] if name=='R-A' else [680,400];page=C[refs[0]]['page']
 for r,a,b in zip(refs,[1,2,3,4],[8,7,6,5]):pins[a]=C[r]['pins']['1'];pins[b]=C[r]['pins']['2']
 rm(s,*refs);add(s,refs[0],'Device:R_Pack04',val,pins,'Resistor_SMD:R_Array_Concave_4x0603',page,pos);s['expected']=copy.deepcopy(list(C.values()))
(P/'phase1/stages.json').write_text(json.dumps(stages,indent=2)+'\n')
print([(s['name'],len(s['expected'])) for s in stages])
